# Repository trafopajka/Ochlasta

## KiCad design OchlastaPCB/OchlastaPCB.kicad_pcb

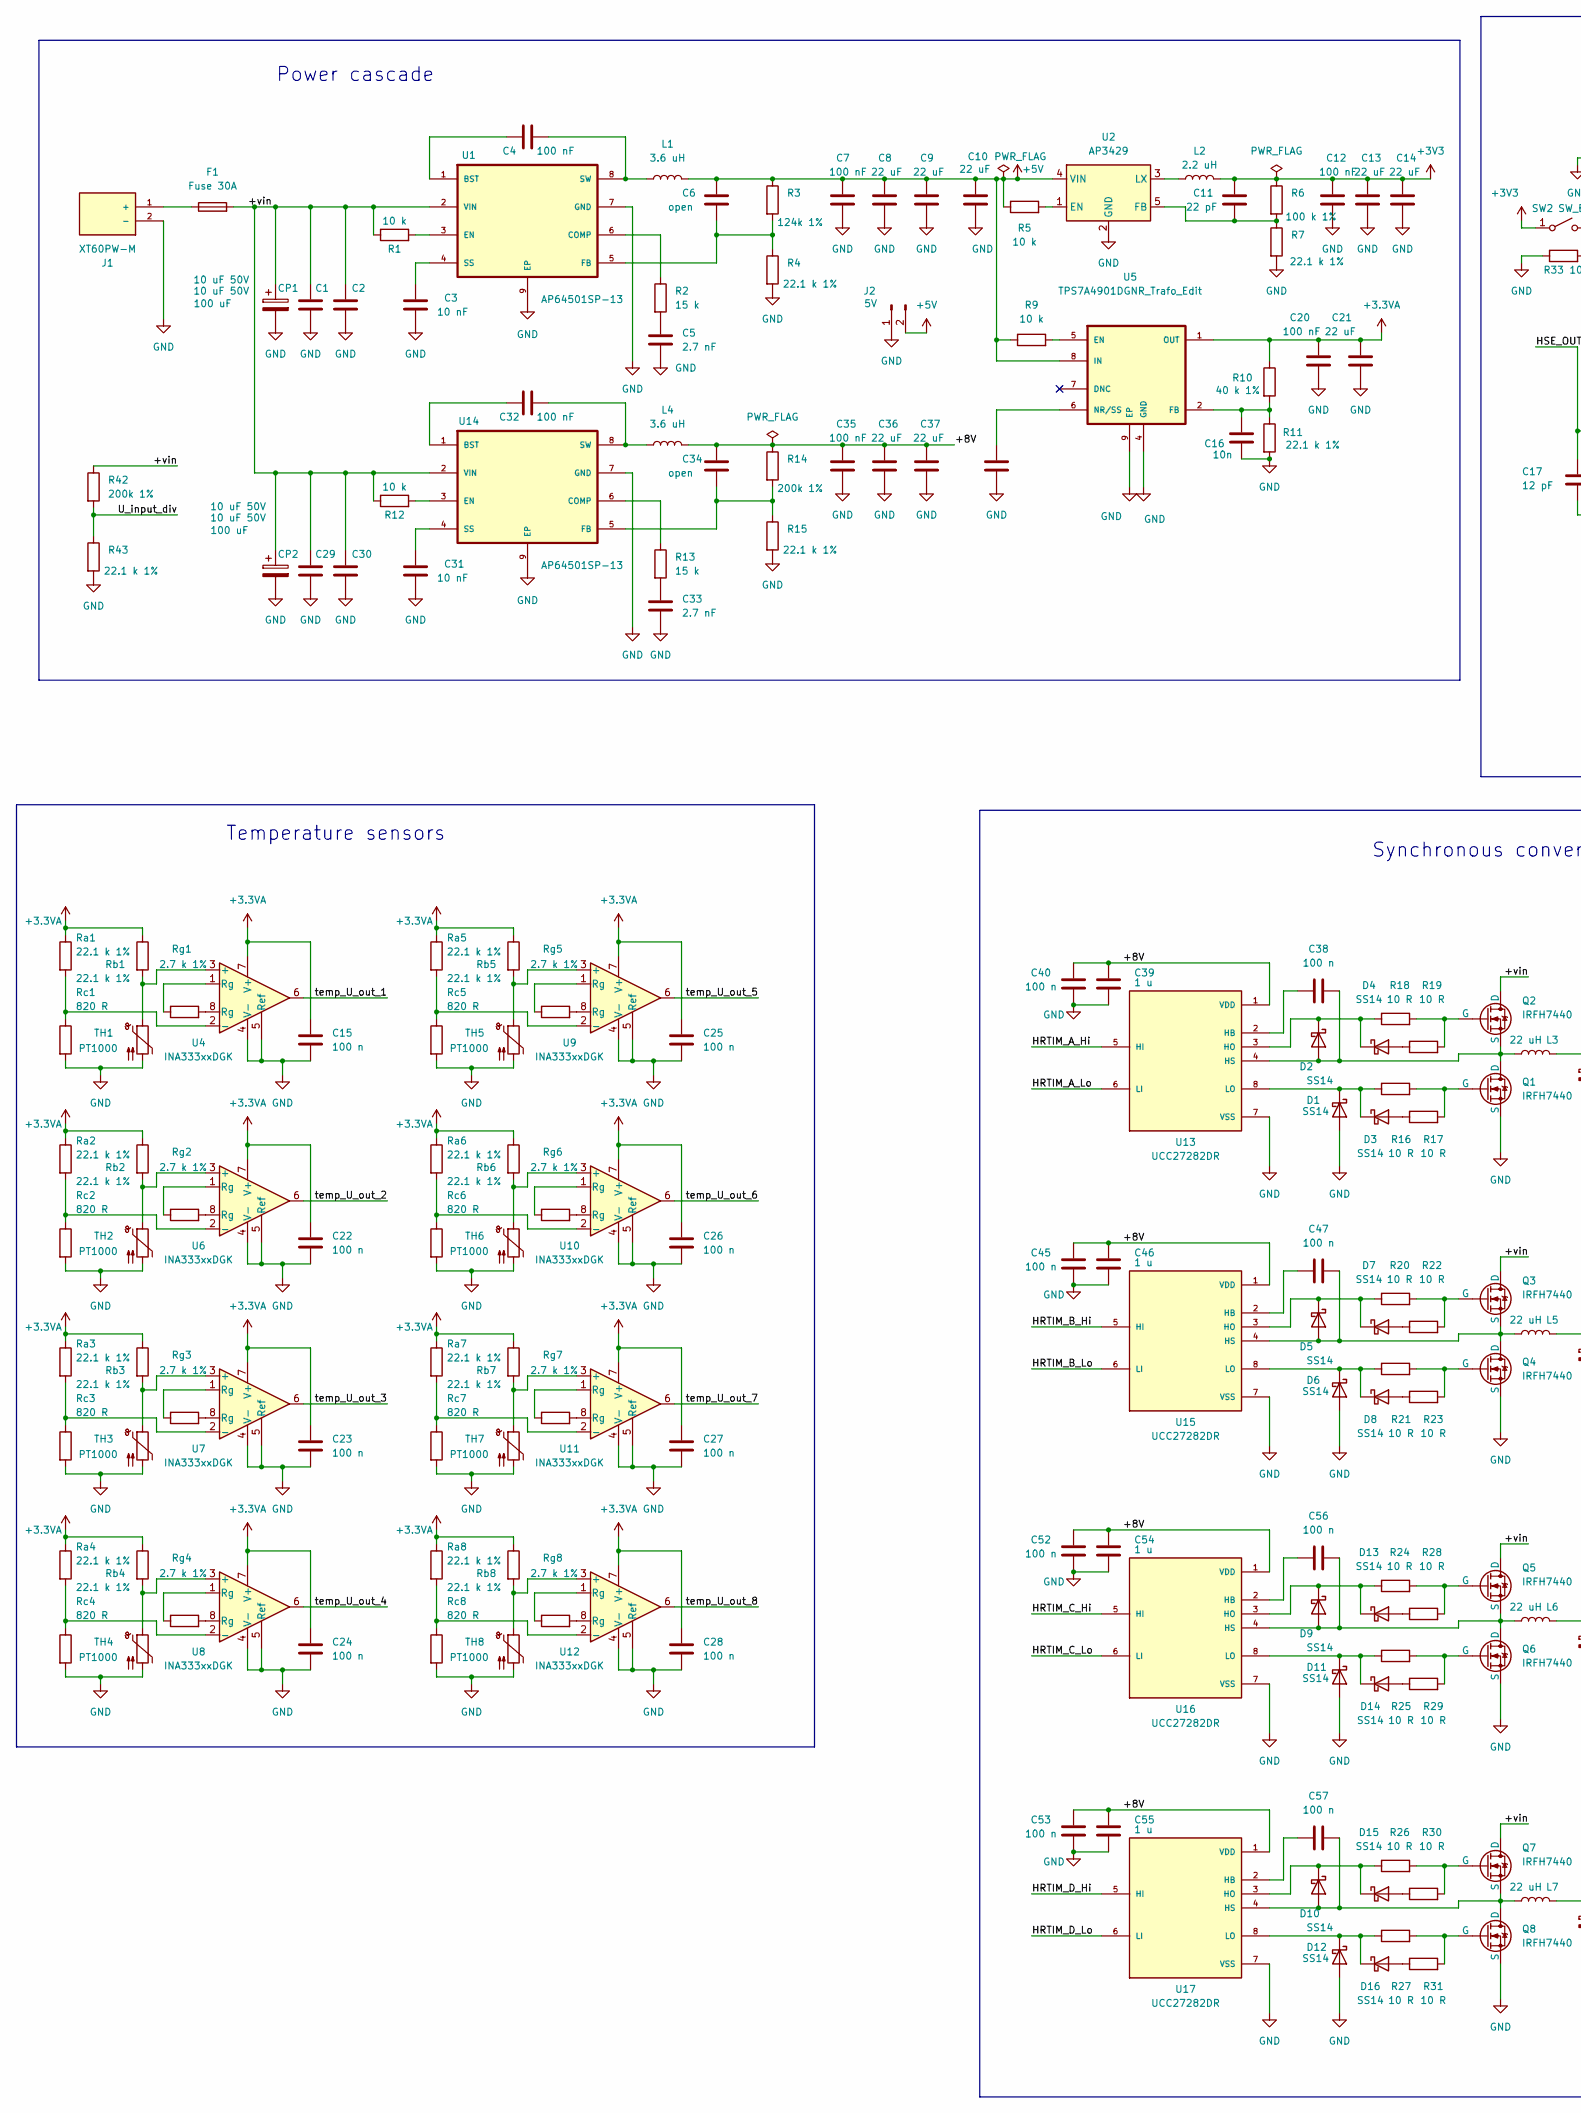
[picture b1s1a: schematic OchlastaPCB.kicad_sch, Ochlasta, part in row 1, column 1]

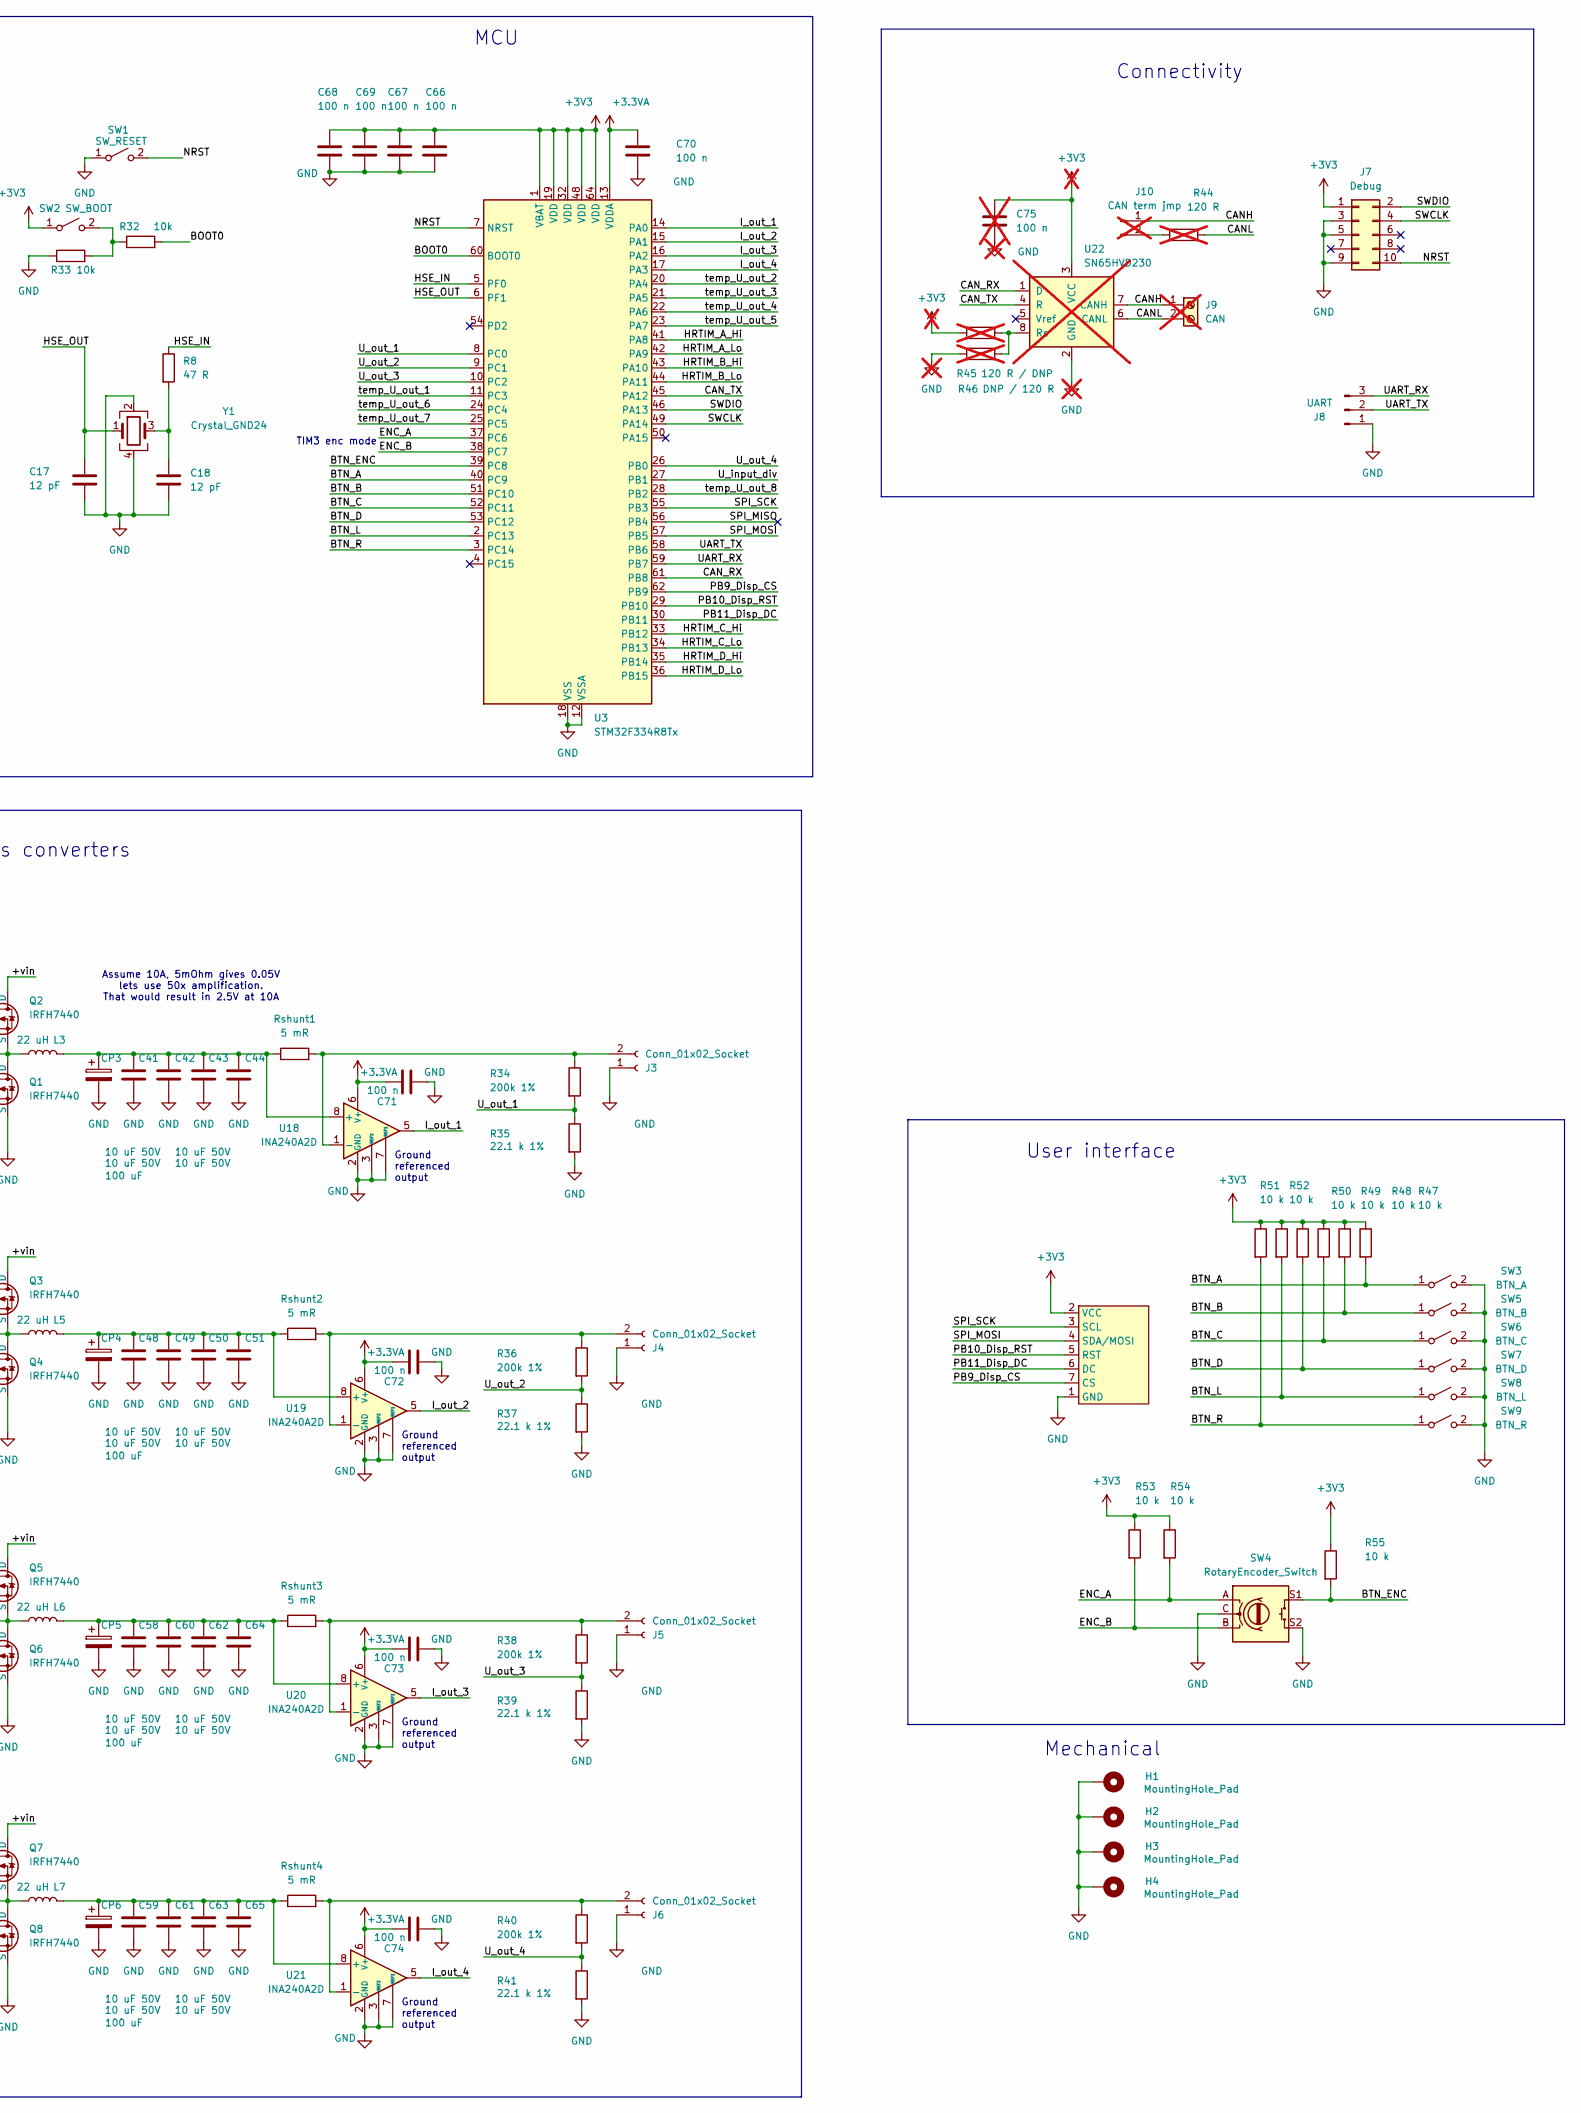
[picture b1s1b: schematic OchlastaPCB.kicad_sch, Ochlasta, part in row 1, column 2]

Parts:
C1, C2, C29, C30, C41, C42, C43, C44, C48, C49, C50, C51, C58, C59, C60, C61, C62, C63, C64, C65: 10 uF 50V; C_1206_3216Metric
C3, C31: 10 nF; C_0603_1608Metric
C4, C7, C12, C20, C32, C35: 100 nF; C_0603_1608Metric
C5, C33: 2.7 nF; C_0603_1608Metric
C6, C34: open; C_0603_1608Metric
C8, C9, C10, C13, C14, C21, C36, C37: 22 uF; C_0805_2012Metric
C11: 22 pF; C_0603_1608Metric
C15, C22, C23, C24, C25, C26, C27, C28, C38, C40, C45, C47, C52, C53, C56, C57, C66, C67, C68, C69, C70, C71, C72, C73, C74: 100 n; C_0603_1608Metric
C16, C19: 10n; C_0603_1608Metric
C17, C18: 12 pF; C_0603_1608Metric
C39, C46, C54, C55: 1 u; C_0603_1608Metric
C75: 100 n; C_0603_1608Metric; not fitted
CP1, CP2, CP3, CP4, CP5, CP6: 100 uF; CP_Elec_8x10
D1, D2, D3, D4, D5, D6, D7, D8, D9, D10, D11, D12, D13, D14, D15, D16: SS14; D_SMA
F1: Fuse 30A; Fuseholder_Keystone_3557
H1, H2, H3, H4: MountingHole_Pad; MountingHole_3.2mm_M3_Pad_Via
J1: XT60PW-M; AMASS_XT60PW-M; PARTREV V1.2
J2: 5V; PinHeader_1x02_P2.54mm_Vertical
J3, J4, J5, J6: Conn_01x02_Socket; TerminalBlock_WAGO_236-402_1x02_P5.00mm_45Degree
J7: Debug; IDC-Header_2x05_P2.54mm_Vertical
J8: UART; PinHeader_1x03_P2.54mm_Vertical
J9: CAN; PhoenixContact_MC_1,5_2-G-3.81_1x02_P3.81mm_Horizontal; not fitted
J10: CAN term jmp; PinHeader_1x02_P2.54mm_Vertical; not fitted
L1, L4: 3.6 uH; L_Changjiang_FNR4030S
L2: 2.2 uH; L_Changjiang_FNR3015S
L3, L5, L6, L7: 22 uH; L_APV_APH1770
Q1, Q2, Q3, Q4, Q5, Q6, Q7, Q8: IRFH7440; PQFN_5x6_FET
R1, R5, R9, R12, R47, R48, R49, R50, R51, R52, R53, R54, R55: 10 k; R_0603_1608Metric
R2, R13: 15 k; R_0603_1608Metric
R3: 124k 1%; R_0603_1608Metric
R4, R7, R11, R15, R35, R37, R39, R41, R43: 22.1 k 1%; R_0603_1608Metric
R6: 100 k 1%; R_0603_1608Metric
R8: 47 R; R_0603_1608Metric
R10: 40 k 1%; R_0603_1608Metric
R14, R34, R36, R38, R40, R42: 200k 1%; R_0603_1608Metric
R16, R17, R18, R19, R20, R21, R22, R23, R24, R25, R26, R27, R28, R29, R30, R31: 10 R; R_0603_1608Metric
R32, R33: 10k; R_0603_1608Metric
R44: 120 R; R_0603_1608Metric; not fitted
R45: 120 R / DNP; R_0603_1608Metric; not fitted
R46: DNP / 120 R; R_0603_1608Metric; not fitted
Ra1, Ra2, Ra3, Ra4, Ra5, Ra6, Ra7, Ra8: 22.1 k 1%; R_0603_1608Metric
Rb1, Rb2, Rb3, Rb4, Rb5, Rb6, Rb7, Rb8: 22.1 k 1%; R_0603_1608Metric
Rc1, Rc2, Rc3, Rc4, Rc5, Rc6, Rc7, Rc8: 820 R; R_0603_1608Metric
Rg1, Rg2, Rg3, Rg4, Rg5, Rg6, Rg7, Rg8: 2.7 k 1%; R_0603_1608Metric
Rshunt1, Rshunt2, Rshunt3, Rshunt4: 5 mR; R_1206_3216Metric
SW1: SW_RESET; SW_Push_SPST_CheapAtJLC
SW2: SW_BOOT; SW_Push_SPST_CheapAtJLC
SW3: BTN_A; SW_PUSH_6mm
SW4: RotaryEncoder_Switch; RotaryEncoder_Alps_EC11E-Switch_Vertical_H20mm
SW5: BTN_B; SW_PUSH_6mm
SW6: BTN_C; SW_PUSH_6mm
SW7: BTN_D; SW_PUSH_6mm
SW8: BTN_L; SW_PUSH_6mm
SW9: BTN_R; SW_PUSH_6mm
TFT1: GMT020-02 TFT Display
TH1, TH2, TH3, TH4, TH5, TH6, TH7, TH8: PT1000; PhoenixContact_MC_1,5_2-G-3.81_1x02_P3.81mm_Horizontal
U1, U14: AP64501SP-13; SOIC127P600X170-9N
U2: AP3429; TSOT-23-5
U3: STM32F334R8Tx; LQFP-64_10x10mm_P0.5mm
U4, U6, U7, U8, U9, U10, U11, U12: INA333xxDGK; VSSOP-8_3x3mm_P0.65mm
U5: TPS7A4901DGNR_Trafo_Edit; SOP65P490X110-9N
U13, U15, U16, U17: UCC27282DR; SOIC127P599X175-8N; PARTREV A
U18, U19, U20, U21: INA240A2D; SOIC-8_3.9x4.9mm_P1.27mm
U22: SN65HVD230; SOIC-8_3.9x4.9mm_P1.27mm; not fitted
Y1: Crystal_GND24; Crystal_SMD_3225-4Pin_3.2x2.5mm

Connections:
+3.3VA: C15.1, C20.1, C21.1, C22.1, C23.1, C24.1, C25.1, C26.1, C27.1, C28.1, C70.1, C71.1, C72.1, C73.1, C74.1, R10.1, Ra1.1, Ra2.1, Ra3.1, Ra4.1, Ra5.1, Ra6.1, Ra7.1, Ra8.1, Rb1.1, Rb2.1, Rb3.1, Rb4.1, Rb5.1, Rb6.1, Rb7.1, Rb8.1, U3.13 (VDDA), U4.7 (V+), U5.1 (OUT), U6.7 (V+), U7.7 (V+), U8.7 (V+), U9.7 (V+), U10.7 (V+), U11.7 (V+), U12.7 (V+), U18.6 (V+), U19.6 (V+), U20.6 (V+), U21.6 (V+)
+3V3: C11.1, C12.1, C13.1, C14.1, C66.1, C67.1, C68.1, C69.1, C75.1, J7.1, L2.2, R6.1, R45.1, R47.1, R48.1, R49.1, R50.1, R51.1, R52.1, R53.1, R54.1, R55.1, SW2.1 (A), TFT1.2 (VCC), U3.1 (VBAT), U3.19 (VDD), U3.32 (VDD), U3.48 (VDD), U3.64 (VDD), U22.3 (VCC)
+5V: C6.1, C7.1, C8.1, C9.1, C10.1, J2.2, L1.2, R3.1, R5.1, R9.1, U2.4 (VIN), U5.8 (IN)
/+8V: C34.1, C35.1, C36.1, C37.1, C39.2, C40.2, C45.2, C46.2, C52.2, C53.2, C54.2, C55.2, L4.2, R14.1, U13.1 (VDD), U15.1 (VDD), U16.1 (VDD), U17.1 (VDD)
/+vin: C1.1, C2.1, C29.1, C30.1, CP1.1, CP2.1, F1.2, Q2.1 (D), Q3.1 (D), Q5.1 (D), Q7.1 (D), R1.1, R12.1, R42.1, U1.2 (VIN), U14.2 (VIN)
/BOOT0: R32.2, U3.60 (BOOT0)
/BTN_A: R47.2, SW3.1 (A), U3.40 (PC9)
/BTN_B: R48.2, SW5.1 (A), U3.51 (PC10)
/BTN_C: R49.2, SW6.1 (A), U3.52 (PC11)
/BTN_D: R50.2, SW7.1 (A), U3.53 (PC12)
/BTN_ENC: R55.2, SW4.S1, U3.39 (PC8)
/BTN_L: R52.2, SW8.1 (A), U3.2 (PC13)
/BTN_R: R51.2, SW9.1 (A), U3.3 (PC14)
/CANH: J9.1, J10.1, U22.7 (CANH)
/CANL: J9.2, R44.2, U22.6 (CANL)
/CAN_RX: U3.61 (PB8), U22.1 (D)
/CAN_TX: U3.45 (PA12), U22.4 (R)
/ENC_A: R54.2, SW4.A, U3.37 (PC6)
/ENC_B: R53.2, SW4.B, U3.38 (PC7)
/HRTIM_A_Hi: U3.41 (PA8), U13.5 (HI)
/HRTIM_A_Lo: U3.42 (PA9), U13.6 (LI)
/HRTIM_B_Hi: U3.43 (PA10), U15.5 (HI)
/HRTIM_B_Lo: U3.44 (PA11), U15.6 (LI)
/HRTIM_C_Hi: U3.33 (PB12), U16.5 (HI)
/HRTIM_C_Lo: U3.34 (PB13), U16.6 (LI)
/HRTIM_D_Hi: U3.35 (PB14), U17.5 (HI)
/HRTIM_D_Lo: U3.36 (PB15), U17.6 (LI)
/HSE_IN: R8.1, U3.5 (PF0)
/HSE_OUT: C17.1, U3.6 (PF1), Y1.1
/I_out_1: U3.14 (PA0), U18.5
/I_out_2: U3.15 (PA1), U19.5
/I_out_3: U3.16 (PA2), U20.5
/I_out_4: U3.17 (PA3), U21.5
/NRST: J7.10, SW1.2 (B), U3.7 (NRST)
/PB9_Disp_CS: TFT1.7 (CS), U3.62 (PB9)
/PB10_Disp_RST: TFT1.5 (RST), U3.29 (PB10)
/PB11_Disp_DC: TFT1.6 (DC), U3.30 (PB11)
/SPI_MISO: U3.56 (PB4)
/SPI_MOSI: TFT1.4 (SDA/MOSI), U3.57 (PB5)
/SPI_SCK: TFT1.3 (SCL), U3.55 (PB3)
/SWCLK: J7.4, U3.49 (PA14)
/SWDIO: J7.2, U3.46 (PA13)
/UART_RX: J8.3, U3.59 (PB7)
/UART_TX: J8.2, U3.58 (PB6)
/U_input_div: R42.2, R43.1, U3.27 (PB1)
/U_out_1: R34.2, R35.1, U3.8 (PC0)
/U_out_2: R36.2, R37.1, U3.9 (PC1)
/U_out_3: R38.2, R39.1, U3.10 (PC2)
/U_out_4: R40.2, R41.1, U3.26 (PB0)
/temp_U_out_1: U3.11 (PC3), U4.6
/temp_U_out_2: U3.20 (PA4), U6.6
/temp_U_out_3: U3.21 (PA5), U7.6
/temp_U_out_4: U3.22 (PA6), U8.6
/temp_U_out_5: U3.23 (PA7), U9.6
/temp_U_out_6: U3.24 (PC4), U10.6
/temp_U_out_7: U3.25 (PC5), U11.6
/temp_U_out_8: U3.28 (PB2), U12.6
GND: C1.2, C2.2, C3.2, C5.2, C7.2, C8.2, C9.2, C10.2, C12.2, C13.2, C14.2, C15.2, C16.2, C17.2, C18.2, C19.2, C20.2, C21.2, C22.2, C23.2, C24.2, C25.2, C26.2, C27.2, C28.2, C29.2, C30.2, C31.2, C33.2, C35.2, C36.2, C37.2, C39.1, C40.1, C41.2, C42.2, C43.2, C44.2, C45.1, C46.1, C48.2, C49.2, C50.2, C51.2, C52.1, C53.1, C54.1, C55.1, C58.2, C59.2, C60.2, C61.2, C62.2, C63.2, C64.2, C65.2, C66.2, C67.2, C68.2, C69.2, C70.2, C71.2, C72.2, C73.2, C74.2, C75.2, CP1.2, CP2.2, CP3.2, CP4.2, CP5.2, CP6.2, D1.2 (A), D6.2 (A), D11.2 (A), D12.2 (A), H1.1, H2.1, H3.1, H4.1, J1.2 (-), J2.1, J3.1, J4.1, J5.1, J6.1, J7.3, J7.5, J7.9, J8.1, Q1.3 (S), Q4.3 (S), Q6.3 (S), Q8.3 (S), R4.2, R7.2, R11.2, R15.2, R33.1, R35.2, R37.2, R39.2, R41.2, R43.2, R46.1, Rc1.2, Rc2.2, Rc3.2, Rc4.2, Rc5.2, Rc6.2, Rc7.2, Rc8.2, SW1.1 (A), SW3.2 (B), SW4.C, SW4.S2, SW5.2 (B), SW6.2 (B), SW7.2 (B), SW8.2 (B), SW9.2 (B), TFT1.1 (GND), TH1.2, TH2.2, TH3.2, TH4.2, TH5.2, TH6.2, TH7.2, TH8.2, U1.7 (GND), U1.9 (EP), U2.2 (GND), U3.12 (VSSA), U3.18 (VSS), U3.31 (VSS), U3.47 (VSS), U3.63 (VSS), U4.4 (V-), U4.5 (Ref), U5.4 (GND), U5.9 (EP), U6.4 (V-), U6.5 (Ref), U7.4 (V-), U7.5 (Ref), U8.4 (V-), U8.5 (Ref), U9.4 (V-), U9.5 (Ref), U10.4 (V-), U10.5 (Ref), U11.4 (V-), U11.5 (Ref), U12.4 (V-), U12.5 (Ref), U13.7 (VSS), U14.7 (GND), U14.9 (EP), U15.7 (VSS), U16.7 (VSS), U17.7 (VSS), U18.2 (GND), U18.3 (REF2), U18.4 (GND), U18.7 (REF1), U19.2 (GND), U19.3 (REF2), U19.4 (GND), U19.7 (REF1), U20.2 (GND), U20.3 (REF2), U20.4 (GND), U20.7 (REF1), U21.2 (GND), U21.3 (REF2), U21.4 (GND), U21.7 (REF1), U22.2 (GND), Y1.2, Y1.4
unnamed: C5.1, R2.2
unnamed: C18.1, R8.2, Y1.3
unnamed: C33.1, R13.2
unnamed: D1.1 (K), D3.1 (K), R16.1, U13.8 (LO)
unnamed: C38.2, D2.2 (A), L3.1, Q1.1 (D), Q2.3 (S), U13.4 (HS)
unnamed: D2.1 (K), D4.1 (K), R18.1, U13.3 (HO)
unnamed: D3.2 (A), R17.1
unnamed: D4.2 (A), R19.1
unnamed: C47.2, D5.2 (A), L5.1, Q3.3 (S), Q4.1 (D), U15.4 (HS)
unnamed: D5.1 (K), D7.1 (K), R20.1, U15.3 (HO)
unnamed: D6.1 (K), D8.1 (K), R21.1, U15.8 (LO)
unnamed: D7.2 (A), R22.1
unnamed: D8.2 (A), R23.1
unnamed: C56.2, D9.2 (A), L6.1, Q5.3 (S), Q6.1 (D), U16.4 (HS)
unnamed: C57.2, D10.2 (A), L7.1, Q7.3 (S), Q8.1 (D), U17.4 (HS)
unnamed: D10.1 (K), D15.1 (K), R26.1, U17.3 (HO)
unnamed: D11.1 (K), D14.1 (K), R25.1, U16.8 (LO)
unnamed: D12.1 (K), D16.1 (K), R27.1, U17.8 (LO)
unnamed: D13.2 (A), R28.1
unnamed: D9.1 (K), D13.1 (K), R24.1, U16.3 (HO)
unnamed: D14.2 (A), R29.1
unnamed: D15.2 (A), R30.1
unnamed: D16.2 (A), R31.1
unnamed: F1.1, J1.1 (+)
unnamed: J3.2, R34.1, Rshunt1.2, U18.1 (-)
unnamed: J4.2, R36.1, Rshunt2.2, U19.1 (-)
unnamed: J5.2, R38.1, Rshunt3.2, U20.1 (-)
unnamed: J6.2, R40.1, Rshunt4.2, U21.1 (-)
unnamed: J10.2, R44.1
unnamed: Q1.2 (G), R16.2, R17.2
unnamed: Q2.2 (G), R18.2, R19.2
unnamed: Q3.2 (G), R20.2, R22.2
unnamed: Q4.2 (G), R21.2, R23.2
unnamed: Q5.2 (G), R24.2, R28.2
unnamed: Q6.2 (G), R25.2, R29.2
unnamed: Q7.2 (G), R26.2, R30.2
unnamed: Q8.2 (G), R27.2, R31.2
unnamed: Rg1.1, U4.1 (Rg)
unnamed: Rg1.2, U4.8 (Rg)
unnamed: Rg2.1, U6.1 (Rg)
unnamed: Rg2.2, U6.8 (Rg)
unnamed: Rg3.1, U7.1 (Rg)
unnamed: Rg3.2, U7.8 (Rg)
unnamed: Rg4.1, U8.1 (Rg)
unnamed: Rg4.2, U8.8 (Rg)
unnamed: Rg5.1, U9.1 (Rg)
unnamed: Rg5.2, U9.8 (Rg)
unnamed: Rg6.1, U10.1 (Rg)
unnamed: Rg6.2, U10.8 (Rg)
unnamed: Rg7.1, U11.1 (Rg)
unnamed: Rg7.2, U11.8 (Rg)
unnamed: Rg8.1, U12.1 (Rg)
unnamed: Rg8.2, U12.8 (Rg)
unnamed: R32.1, R33.2, SW2.2 (B)
unnamed: C4.1, U1.1 (BST)
unnamed: R2.1, U1.6 (COMP)
unnamed: R1.2, U1.3 (EN)
unnamed: C6.2, R3.2, R4.1, U1.5 (FB)
unnamed: C3.1, U1.4 (SS)
unnamed: C4.2, L1.1, U1.8 (SW)
unnamed: R5.2, U2.1 (EN)
unnamed: C11.2, R6.2, R7.1, U2.5 (FB)
unnamed: L2.1, U2.3 (LX)
unnamed: Rb1.2, TH1.1, U4.3 (+)
unnamed: Ra1.2, Rc1.1, U4.2 (-)
unnamed: R9.2, U5.5 (EN)
unnamed: C16.1, R10.2, R11.1, U5.2 (FB)
unnamed: C19.1, U5.6 (NR/SS)
unnamed: Rb2.2, TH2.1, U6.3 (+)
unnamed: Ra2.2, Rc2.1, U6.2 (-)
unnamed: Rb3.2, TH3.1, U7.3 (+)
unnamed: Ra3.2, Rc3.1, U7.2 (-)
unnamed: Rb4.2, TH4.1, U8.3 (+)
unnamed: Ra4.2, Rc4.1, U8.2 (-)
unnamed: Rb5.2, TH5.1, U9.3 (+)
unnamed: Ra5.2, Rc5.1, U9.2 (-)
unnamed: Rb6.2, TH6.1, U10.3 (+)
unnamed: Ra6.2, Rc6.1, U10.2 (-)
unnamed: Rb7.2, TH7.1, U11.3 (+)
unnamed: Ra7.2, Rc7.1, U11.2 (-)
unnamed: Rb8.2, TH8.1, U12.3 (+)
unnamed: Ra8.2, Rc8.1, U12.2 (-)
unnamed: C38.1, U13.2 (HB)
unnamed: C32.1, U14.1 (BST)
unnamed: R13.1, U14.6 (COMP)
unnamed: R12.2, U14.3 (EN)
unnamed: C34.2, R14.2, R15.1, U14.5 (FB)
unnamed: C31.1, U14.4 (SS)
unnamed: C32.2, L4.1, U14.8 (SW)
unnamed: C47.1, U15.2 (HB)
unnamed: C56.1, U16.2 (HB)
unnamed: C57.1, U17.2 (HB)
unnamed: C41.1, C42.1, C43.1, C44.1, CP3.1, L3.2, Rshunt1.1, U18.8 (+)
unnamed: C48.1, C49.1, C50.1, C51.1, CP4.1, L5.2, Rshunt2.1, U19.8 (+)
unnamed: C58.1, C60.1, C62.1, C64.1, CP5.1, L6.2, Rshunt3.1, U20.8 (+)
unnamed: C59.1, C61.1, C63.1, C65.1, CP6.1, L7.2, Rshunt4.1, U21.8 (+)
unnamed: R45.2, R46.2, U22.8 (Rs)

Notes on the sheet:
Temperature sensors
Power cascade
User interface
Ground referenced output
Connectivity
MCU
Synchronous converters
Mechanical
TIM3 enc mode
Assume 10A, 5mOhm gives 0.05V lets use 50x amplification. That would result in 2.5V at 10A

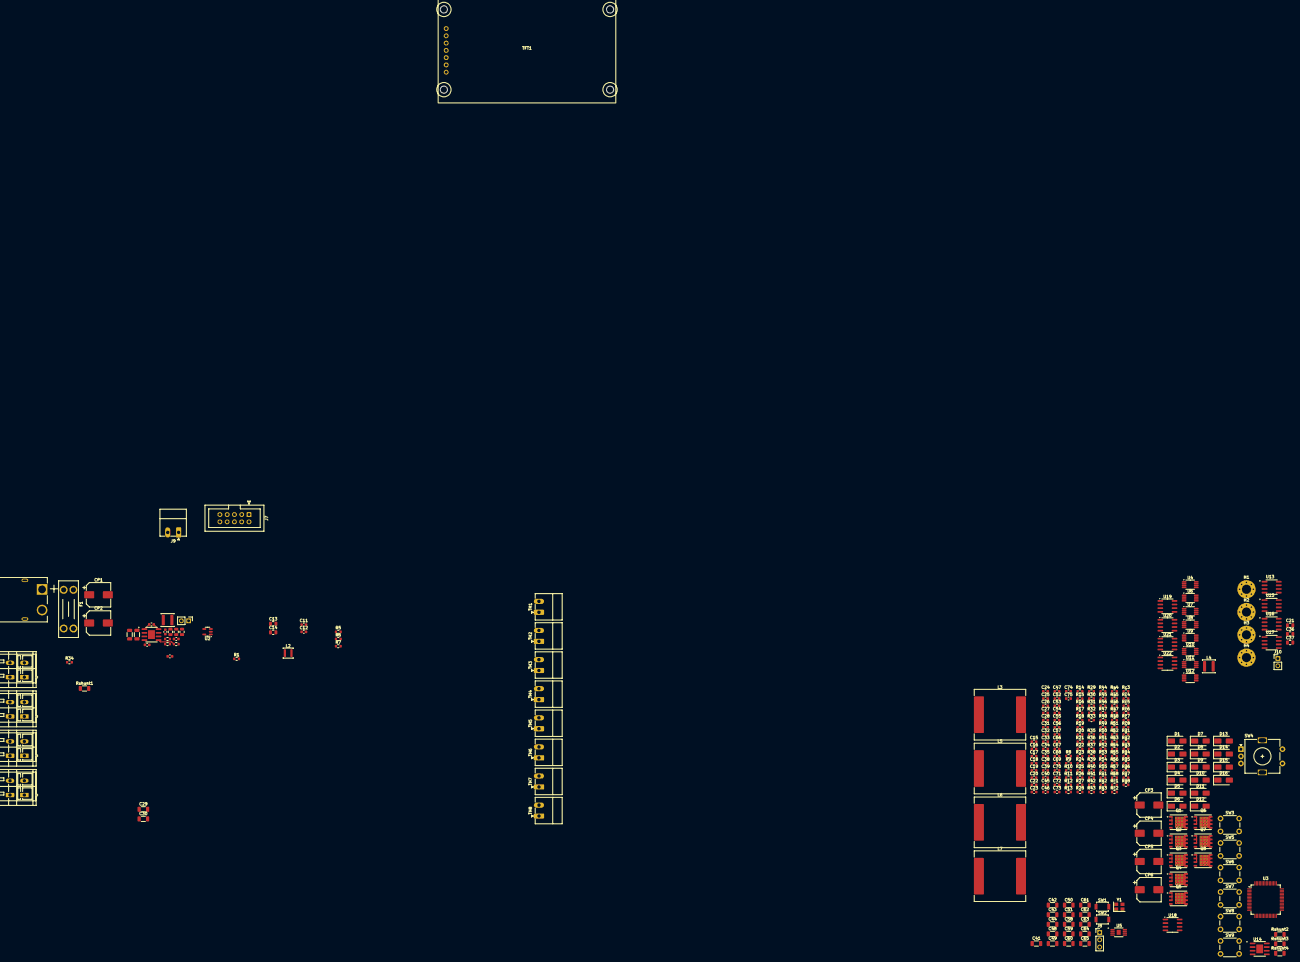
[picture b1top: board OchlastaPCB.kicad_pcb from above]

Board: 4 copper layers, 259 parts (0 on the bottom side), 154 nets.

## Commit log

2025-09-04 Starting to brainstorm
2025-10-09 some brainstorming ideas for HW
2025-10-09 MCU pins first thoughts
2025-10-11 Preliminary MCU pinout
2025-10-27 Power cascade for MCU schematics, created few components...
2025-10-27 preliminary Pt1000 analog readout circuitry design and calculation in jupyter notebook
2025-10-30 Precision LDO for analog circuitry in schematics
2025-11-04 Schematics for one channel of main buck converter done I guess
2025-11-08 Schematics done except for CAN transciever
2025-11-10 Schematics complete I guess
2025-11-10 Schematics seems finished, starting PCB design
